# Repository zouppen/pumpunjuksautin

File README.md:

# Pumpunjuksautin - Defrauding heat pumps for fun and profit

## Introduction
Pumpunjuksautin is a device for introducing a measure of load control into
heating systems where no external control features such as automation buses
exist. The core idea is to modify the signal the heating controller gets from
the thermistor measuring it's warm water accumulator temperature. By modifying
this signal so that the accumulator seems warmer than it is in actuality, the
heating can be impeded until the desired time.

In practice, Pumpunjuksautin is meant to be attached to Modbus RTU bus, through
which it is controlled by building automation. Typically the heating duty cycle
is delayed until either energy market or solar power generation allow for cost
efficient heating.

## Repository content
This repository contains the design of the whole Pumpunjuksautin device,
divided to it's components:
* [Firmware source code](avr/)
* [Documentation](docs/)
* [Enclosure design](enclosure/README.md)
* [Printed circuit board design](pcb/)
* [Operational utilities](juksutil/) (JuksUtil)

## License
The contents of this repository are licensed under the GNU General Public
License version 3 or later. See file LICENSE for the license text.

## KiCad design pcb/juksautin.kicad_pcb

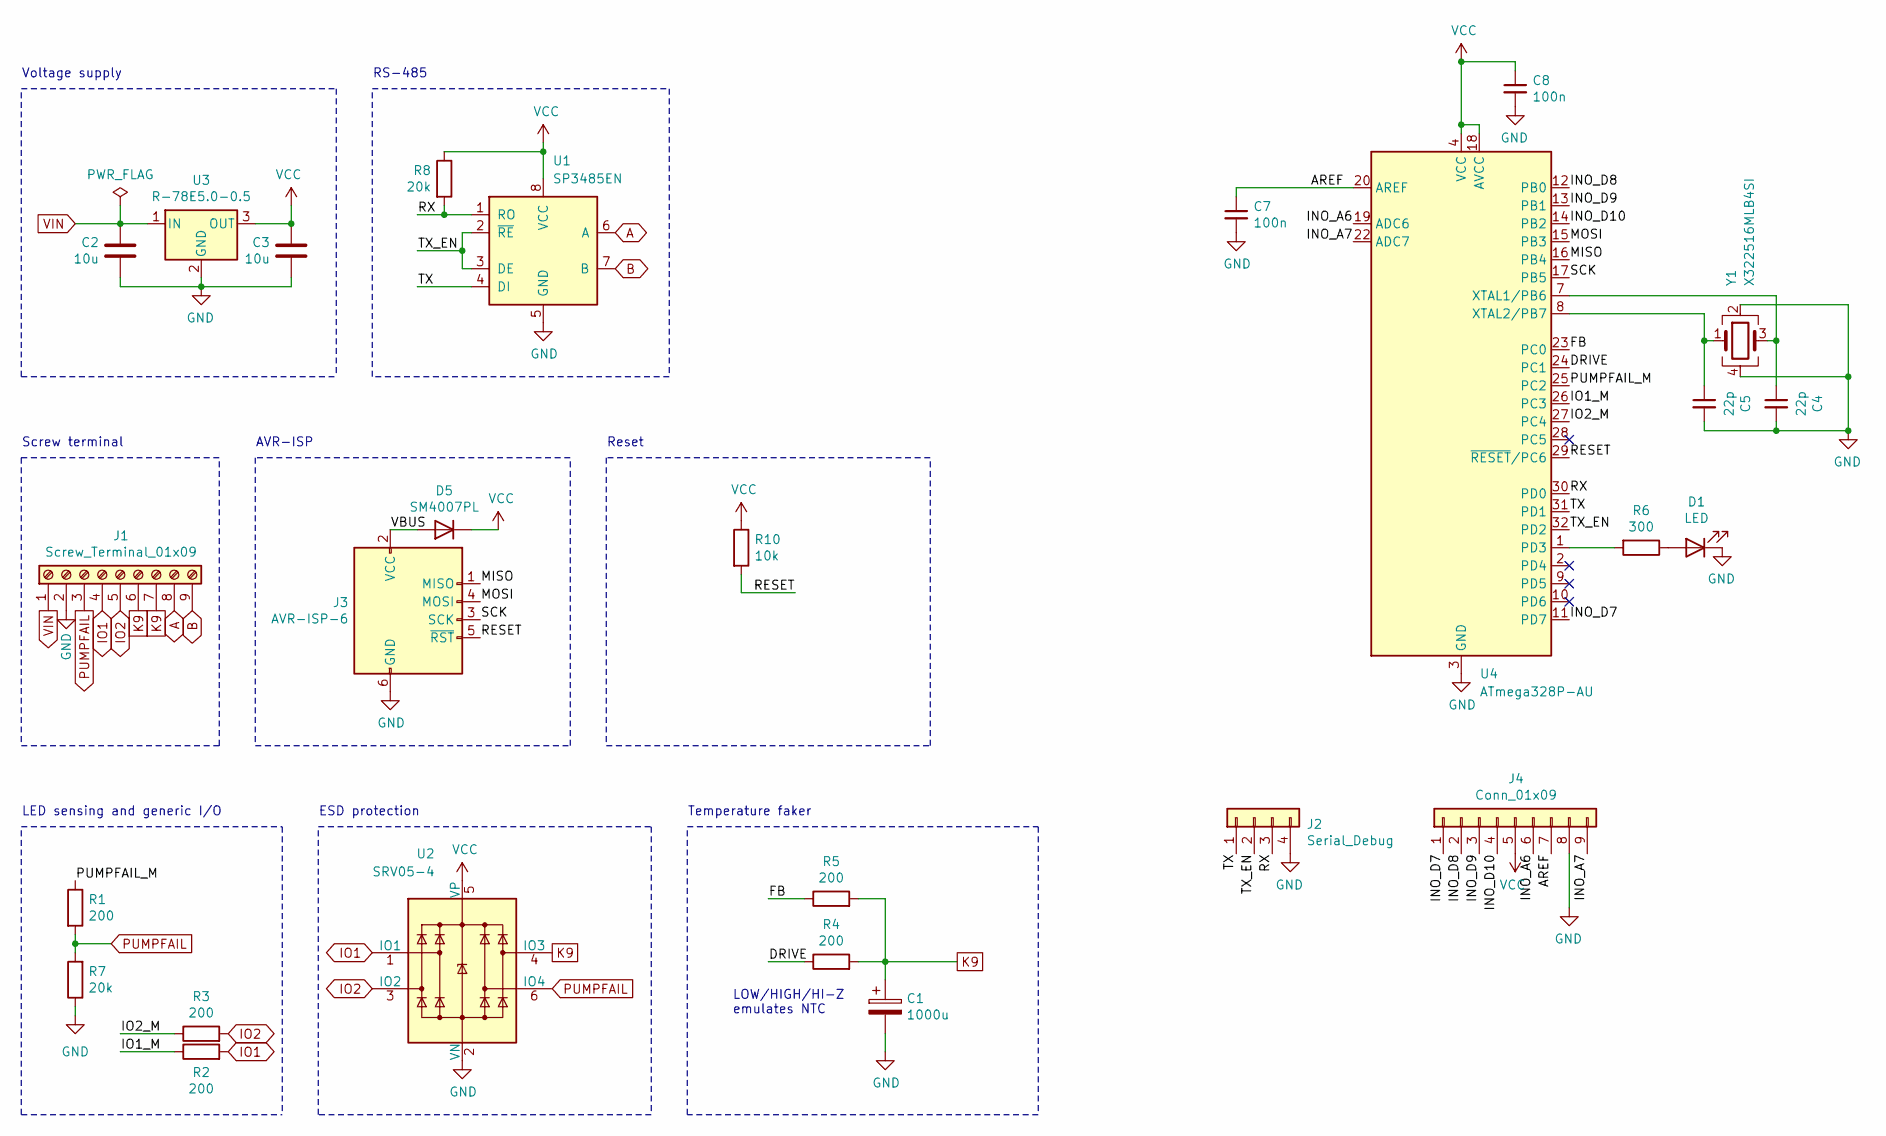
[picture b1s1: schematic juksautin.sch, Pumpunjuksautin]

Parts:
C1: 1000u; CP_Elec_8x10; LCSC C134755
C2, C3: 10u; C_1206_3216Metric; LCSC C13585
C4, C5: 22p; C_0402_1005Metric; LCSC C1555
C7, C8: 100n; C_0402_1005Metric; LCSC C1525
D1: LED; LED_0603_1608Metric; LCSC C72043
D5: SM4007PL; D_SOD-123F; LCSC C64898
J1: Screw_Terminal_01x09; PhoenixContact_MC_1,5_9-G-3.81_1x09_P3.81mm_Horizontal
J2: Serial_Debug; PinHeader_1x04_P1.27mm_Vertical
J3: AVR-ISP-6; PinHeader_2x03_P2.54mm_Horizontal
J4: Conn_01x09; PinHeader_1x09_P2.54mm_Vertical
R1, R2, R3, R4, R5: 200; R_0603_1608Metric; LCSC C8218
R6: 300; R_0603_1608Metric; LCSC C23025
R7, R8: 20k; R_0603_1608Metric; LCSC C4184
R10: 10k; R_0603_1608Metric; LCSC C25804
U1: SP3485EN; SOIC-8_3.9x4.9mm_P1.27mm; LCSC C8963
U2: SRV05-4; SOT-23-6; LCSC C85364
U3: R-78E5.0-0.5; Converter_DCDC_RECOM_R-78E-0.5_THT
U4: ATmega328P-AU; TQFP-32_7x7mm_P0.8mm
Y1: X322516MLB4SI; Crystal_SMD_3225-4Pin_3.2x2.5mm

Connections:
/AREF: C7.1, J4.7, U4.20 (AREF)
/DRIVE: R4.1, U4.24 (PC1)
/FB: R5.1, U4.23 (PC0)
/INO_A6: J4.6, U4.19 (ADC6)
/INO_A7: J4.9, U4.22 (ADC7)
/INO_D7: J4.1, U4.11 (PD7)
/INO_D8: J4.2, U4.12 (PB0)
/INO_D9: J4.3, U4.13 (PB1)
/INO_D10: J4.4, U4.14 (PB2)
/IO1_M: R2.1, U4.26 (PC3)
/IO2_M: R3.1, U4.27 (PC4)
/MISO: J3.1 (MISO), U4.16 (PB4)
/MOSI: J3.4 (MOSI), U4.15 (PB3)
/PUMPFAIL_M: R1.1, U4.25 (PC2)
/RESET: J3.5 (~RST), R10.2, U4.29 (~RESET~/PC6)
/RX: J2.3, R8.2, U1.1 (RO), U4.30 (PD0)
/SCK: J3.3 (SCK), U4.17 (PB5)
/TX: J2.1, U1.4 (DI), U4.31 (PD1)
/TX_EN: J2.2, U1.2 (~RE~), U1.3 (DE), U4.32 (PD2)
/VBUS: D5.2 (A), J3.2 (VCC)
A: J1.8, U1.6 (A)
B: J1.9, U1.7 (B)
GND: C1.2, C2.2, C3.2, C4.2, C5.2, C7.2, C8.2, D1.1 (K), J1.2, J2.4, J3.6 (GND), J4.8, R7.1, U1.5 (GND), U2.2 (VN), U3.2 (GND), U4.3 (GND), U4.5 (GND), U4.21 (GND), Y1.2, Y1.4
IO1: J1.4, R2.2, U2.1 (IO1)
IO2: J1.5, R3.2, U2.3 (IO2)
K9: C1.1, J1.6, J1.7, R4.2, R5.2, U2.4 (IO3)
unnamed: C4.1, U4.7 (XTAL1/PB6), Y1.3
unnamed: C5.1, U4.8 (XTAL2/PB7), Y1.1
unnamed: D1.2 (A), R6.1
unnamed: R6.2, U4.1 (PD3)
PUMPFAIL: J1.3, R1.2, R7.2, U2.6 (IO4)
VCC: C3.1, C8.1, D5.1 (K), J4.5, R8.1, R10.1, U1.8 (VCC), U2.5 (VP), U3.3 (OUT), U4.4 (VCC), U4.6 (VCC), U4.18 (AVCC)
VIN: C2.1, J1.1, U3.1 (IN)

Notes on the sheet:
LOW/HIGH/HI-Z emulates NTC
LED sensing and generic I/O
Temperature faker
Screw terminal
RS-485
Voltage supply
ESD protection
AVR-ISP
Reset

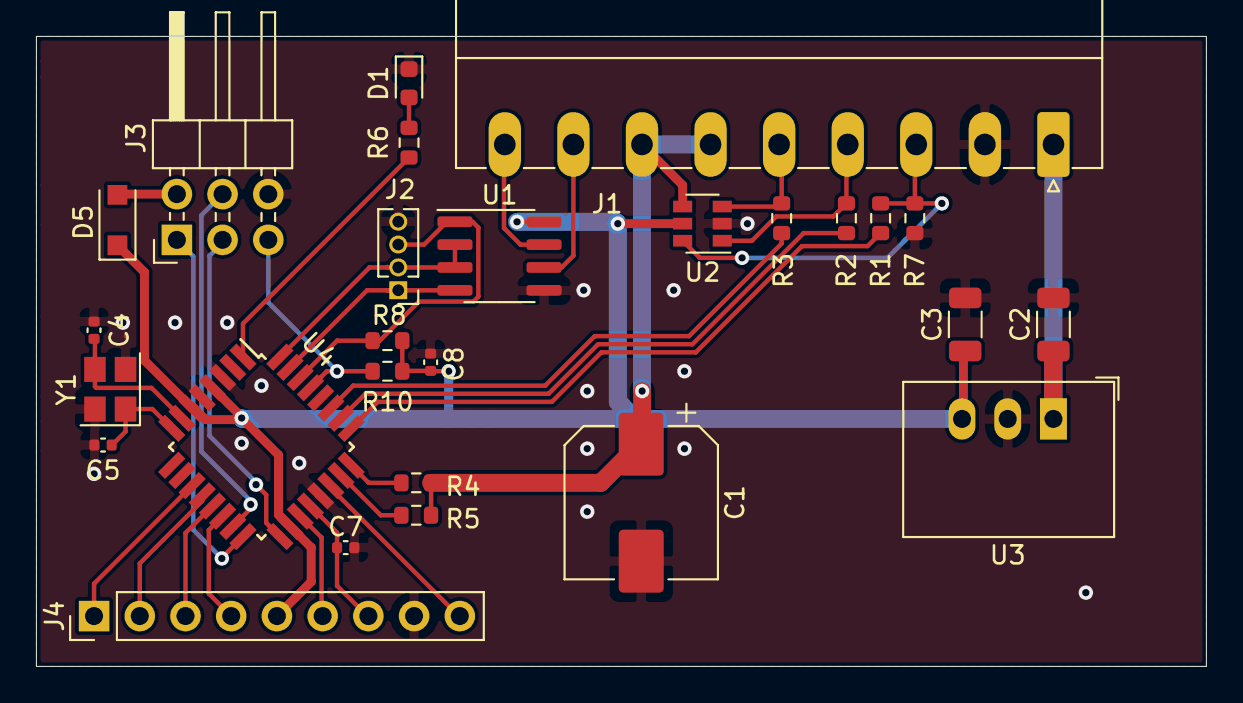
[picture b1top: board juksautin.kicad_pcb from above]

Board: 2 copper layers, 65.0 x 35.0 mm, 27 parts (0 on the bottom side), 33 nets.

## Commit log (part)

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2021-05-16 Initial doc
2021-05-16 Try inline math
2021-05-16 Subscript
2021-05-16 LARGE FONT
2021-05-16 Fake lower temperatures howto
2021-05-17 Din rail enclosure
2021-05-17 Add enclosure documentation
2021-05-19 enclosure: Make the front panel to fill the whole front side by making a 1mm step
2021-05-28 pcb: Make the board two-layer instead of one
2021-06-02 pcb: Rename K5 to K9 everywhere
2021-06-03 pcb: Rerouting and cleanup
2021-06-04 Atmega328 based pcb layed out
2021-06-04 pcb: Replace IDC-6 connector with plain pins. The casing is 3D printed.
2021-06-07 enclosure: Make full-height dent
2021-06-07 Add IDC connector instead of USB
2021-06-13 avr: Allow setting target voltage via serial
2021-06-14 Count juksautus correctly. Optimize order to make it start measuring earlier.
2021-06-15 avr: Accumulate measurements, make better debug prints
2021-06-15 avr: Update comments
2021-06-15 avr: Use nice pin macros supporting pin defines, too
    Allows us to lift requirement to Arduino digitalWrite and pinMode
2021-06-15 avr: Remove (almost all) traces of C++ and make it C99 compliant
    Serial is still there but we take it out soon.
2021-06-17 Schema and layout fixes after v0.9
    - Crystal Y1 symbol changed to 4-pin, affecting the wiring as well
    - Remove DC block capacitor C6, blocked RESET signal
2021-06-19 avr: Move FB pin initialization for clarity and improve comment
2021-06-19 avr: Partially working RS-485 comms
    Please note this freezes weirdly. Needs debugging and clean-up.
2021-06-19 avr: Optimize serial tx, make RS-485 handover work
    Fill in TX 1-byte buffer right after the tx starts (UDRE_vect). Use
    TX_vect to switch to receive mode after all has been sent.
2021-06-19 avr: Add simple sleep mode, not turning off any timers etc.
2021-06-19 avr: Reorganized serial comms to serial.c but I broke something
    This is not properly working at the moment. Needs debugging. It
    compiles, though.
2021-06-19 pcb: Remove old Arduino / Atmega32u4 based pcb cad files
2021-06-20 avr: Use LTO and C17
2021-06-20 avr: Add debug print of received frame to understand the tx/rx issue
2021-06-20 avr: Improve serial comments
2021-06-20 avr: Make serial_tx_start internally atomic to avoid issues
2021-06-20 avr: Serial receive shouldn't need serial disabling
2021-06-21 pcb: Remove reset pad (we have header anyway) and and RX pull-up
    RX pull-up seems to be required to keep RX HIGH during transmit phase
    when SP3485 is HI-Z.
2021-06-27 avr: No functional changes, clean-up
2021-06-27 avr: Add Arduino pin to hardware config as an example
2021-06-27 avr: Meanwhile:x print everything we received on error
2021-06-28 avr: Improve readability of clock.c
2021-06-29 avr: Make enums as short as possible
2021-07-01 avr: Move ADC functions to own module
2021-07-01 Prepare ADC_vect ISR for moving to adc.c
2021-07-01 avr: Move ADC_vect out of main to ADC
2021-07-03 avr: Outside thermistor measurement
2021-07-03 avr: String formatting corrections
2021-07-03 avr: Add error LED read
2021-08-20 Improve double buffering by protecting the front buffer at all costs.
    If there's an overflow, error counter is increased and one frame is
    discarded.
2021-08-20 avr: Important fix in timer comments The unit is not milliseconds!
2021-08-20 avr: Move definitions to CMake from the source file
2021-08-20 avr: Validate clock parameters in CMake instead of cpp.
    This makes the error messages clearer and make them appear in ccmake
    and others instead of a compile-time failure.
2021-08-20 avr: Make the receiver cut the packets using timeouts instead of newlines
2021-09-01 avr: Add VERSION command to build-time version from Git
2021-09-01 Added GPLv3 text and "GPLv3 or later" copyright header in source files
    Fixes #1
2021-09-02 avr: Put all strings in serial comms to PROGMEM
2021-09-02 Move LICENSE file to root directory.
    All the sources are GPLv3, the only exception is stated in the
    enclosure directory, which is Creative Commons, but not sharealike so
    it's safe for GPL.
2021-09-02 tools: Use the rawest possible mode in socat
2021-09-03 avr: Fix a problem with Eastern non-DST zones such as Asia/Tokyo #9
2021-09-03 avr: Clean up unnecessary NUL termination checks and ellipses after #2
2021-09-04 avr: Improve serial line sending
    - Use > instead of .. for marking too long messages
    - Do not send messages which are not NUL terminated at all
    - Some tidying
2021-09-04 avr: Update comments. Remove redundant comments #10
    There is no point in having comments which are obvious by reading the
    code.
2021-09-04 Move docs to docs/ and add initial draft for Modbus registers #12
2021-09-04 docs: Modbus table #12
2021-09-04 docs: Use monospace in registers #12
2021-09-04 docs: Edit modbus.md harder #12
2021-09-05 docs: Modbus table formatting and adding of time related registers #12
2021-09-06 Use char* instead of uint8_t* in serial buffers. Closes #13
    At first it was the best idea ever but since heavy use of string.h
    functions, uint8_t buffers are causing type casts here and there, so
    be a little practical over pureness.
2021-09-07 avr: Prevent including headers multiple times #10
2021-09-08 avr cmd: Provide list length and fix scanner function type #5
2021-09-08 avr: Add simple interface function for just blinking the LED #5
2021-09-08 Added some modbus register suggestions #12
2021-09-08 avr: Make scanner related error in ASCII interface clearer #5
2021-09-09 avr: Implement ASCII read support #5
2021-09-09 avr clock: Do not mess TIMER2 counter. It affects serial timing
    The lost extra accuracy is normally 256*250/16e6* = 4ms when setting
    clock time. It is insignificat because the serial communication is so
    slow so the clock time is old before it reaches the MCU.
2021-09-09 avr: Naming change, clock -> time to match the public interface #10
2021-09-09 avr: Modbus functions for time setting #16
2021-09-10 avr: Define macro for bswaps, not using __builtin directly #10
    Do it like on GNU systems in byteswap.h, but without fallback. We are
    using GCC anyway. In case this breaks, copy the fallbacks from the
    byteswap.h in a desktop system.
2021-09-10 avr: Introduce ENSURE_COUNT macro to avoid repetitive code #10
    This also stores the expected count to a static variable. Useful in
    future for parse error message formatting.
2021-09-10 avr: Relax the const requirement in scanner function.
    Some scanners which need to tokenize the input further do need to edit
    the data in-place to avoid use of dynamic memory. Let them do so.
2021-09-10 avr: Add version command for ASCII protocol #5
2021-09-10 Make commands.tsv simpler by stripping repetitive prefixes
2021-09-10 avr: Separate juksautus specific functions out of main #10
2021-09-11 avr: Make round robin counter in ADC static #10
    This ensures we are not messing the ADC cycles in case juksautin.count
    gets cleaned by a user command.
2021-09-11 avr: Make accumulators to drop bits if they run full. Closes #18
    This patch defines a certain high water level mark for the accumulator
    when the least significant bits of both divident and divisor are
    thrown away to give more room. This of course affects the mean
    calculation but with so unnoticable amount.
    So it doesn't make a great difference in math frees the user from
    handling errors related to overflown counters.
2021-09-11 avr: Add comment #10
2021-09-12 avr: Add function for getting current target value
2021-09-12 avr: Improve indentation and comments #10
2021-09-12 avr: Add support for scanning and printing of int16
2021-09-12 avr: Add ASCII commands ffor reading K5, K9, and outside temperature #5
2021-09-12 avr: Make serial buffers one line long (80). Should easily fit those.
2021-09-13 avr: Remove the support for comma separated values
    The function was pretty but unnecessarily complicated. We don't have
    the need for writing multiple values at the same time and it's kind of
    against the spirit of Modbus.
2021-09-13 avr: Round towards nearest integer in target setter and getter
2021-09-13 avr: Make error message volatile to avoid optimization
    There's a real risk that process_write would believe the error variable
    access might be optimized away.
2021-09-13 avr: Detect if time string cut short
2021-09-13 avr: Report serial overflows
2021-09-13 Remove printf float support
2021-09-14 avr: Use "#pragma once" instead of legacy ifndef-define #10
    https://en.wikipedia.org/wiki/Pragma_once
    https://gcc.gnu.org/onlinedocs/cpp/Pragmas.html#index-_0023pragma-once
2021-09-14 Add rudimentary README
    Fixes #8
2021-09-18 Make the build depend on generator script changes #10
    For some reason, executable rights or so, without
    CMAKE_CURRENT_SOURCE_DIR explicit declaration it doesn't detect
    changes in the file.
2021-09-18 avr: Indicator LED is considered part of Juksautin hardware and belongs there
2021-09-19 avr: Fix types in time functions
2021-09-19 avr: Add data type for string to make the command interface consistent
2021-09-19 avr: There is no more entries which are only Modbus accessible
2021-09-19 avr: Move non-juksautin functions to misc.c
2021-09-19 avr: Add byteswap.h
2021-09-20 Fix types and data lengths in the Modbus mock-up #16
2021-09-20 avr: Fix Modbus function type parser #16
2021-09-20 avr: Do not erase EEPROM on every flashing
    To activate this change you need to run `make fuses`
2021-09-20 avr: Make fill_exception work without knowledge of function code #16
    Modbus function codes are not the same as modbus_type_t enum. So we
    need to make it independent. The serial buffer is already populated so
    it's easy to just stuff it there.
    Doing bitwise operation so if it gets called multiple times, the
    integer is not overflown but just gives the same result.
2021-09-20 avr: Shorten trivial variable name and improve comments #10
2021-09-20 avr: Add support for Preset Multiple Registers (FC=16) #16
2021-09-21 avr: Changes in the register table #16
    Disable the boolean register until we have support for it. This
    doesn't affect ASCII protocol but allows the project to compile.
    Make all the read-only registers input registers instead of holding
    registers.
2021-09-21 avr: Introduce dummy coil for testing purposes.
2021-09-21 Change misleading variable name in modbus write registers #10
2021-09-21 avr: Add support for Modbus function code 0x02 Read Input Status #16
2021-09-21 avr: Add support for writing muliple coils (function code 0x0F) closes #16
2021-09-22 avr: Fix timing error of 24 ms (4*(256-250)) when setting the clock
2021-09-23 juksutil: Improve naming of struct fields
2021-09-23 juksutil: Fix problem with time zone Asia/Tehran
    It has transitions already after year 2038 so have to be careful with
    the data types.
2021-09-24 juksutil: Fix NULL pointer exception when accidentally a mmapping a directory
2021-09-25 juksutil: Do not crash in case of a directory
2021-09-25 juksutil: Make it work on UTC zone as well (no transitions at all)
2021-09-25 juksutil: Remove unnecessary debug print and use correct data types
2021-09-26 juksutil: Formatting of show-transition command output
2021-09-26 juksutil: Small changes to cmdline parser
2021-09-26 Put CMake build dir to gitignore
2021-09-28 avr: Deliver function code via an argument
2021-09-29 juksutil: Move Modbus initialization out of command function
2021-09-29 avr: Move OK message out of the write handler
2021-09-29 avr: Add support for tx skip. Can be used for Modbus
2021-09-29 avr: Special non-standard Modbus command for ASCII requests
2021-09-30 avr: Make the prototype match the definition #10
2021-09-30 juksutil: Use names line_in and line_out for clarity #10
2021-09-30 avr: Fix variadic macro.
    Using legacy format because avr-gcc isn't new enough
2021-10-01 juksutil: Improve the cmd_ascii. Cancel the timer, too.
2021-10-01 juksutil: Future-proof by using time_t instead of uint32_t
    We are using uint32 on the hardware anyway but not going to make
    choices which would require large changes to utils if we switch to 64
    bit values in the future.
2021-10-01 juksutil: Move serial initialization to its own function #10
2021-10-01 juksutil: Improve error message and make sure len is 0
2021-10-02 juksutil: Use libmodbus macros instead of hand-written ones bit tricks #10
2021-10-02 juksutil: Rename sync-clock to sync-time
2021-10-03 Add README for JuksUtil
2021-10-03 juksutil: Use glib allocation instead of asprintf
2021-10-03 juksutil: For date to get better date parsing facility than libc
    The point is the parsing function is part of Gnulib which would be
    license compatible but too much work. It's better to just fork that
    command for this kind of seldom-used feature.
2021-10-03 juksutil: Yet another OCD change to date output formatting
